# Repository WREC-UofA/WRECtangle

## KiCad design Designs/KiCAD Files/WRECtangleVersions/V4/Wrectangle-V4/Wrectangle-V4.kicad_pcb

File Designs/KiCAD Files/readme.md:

This is where we'll put KiCAD projects / updates.

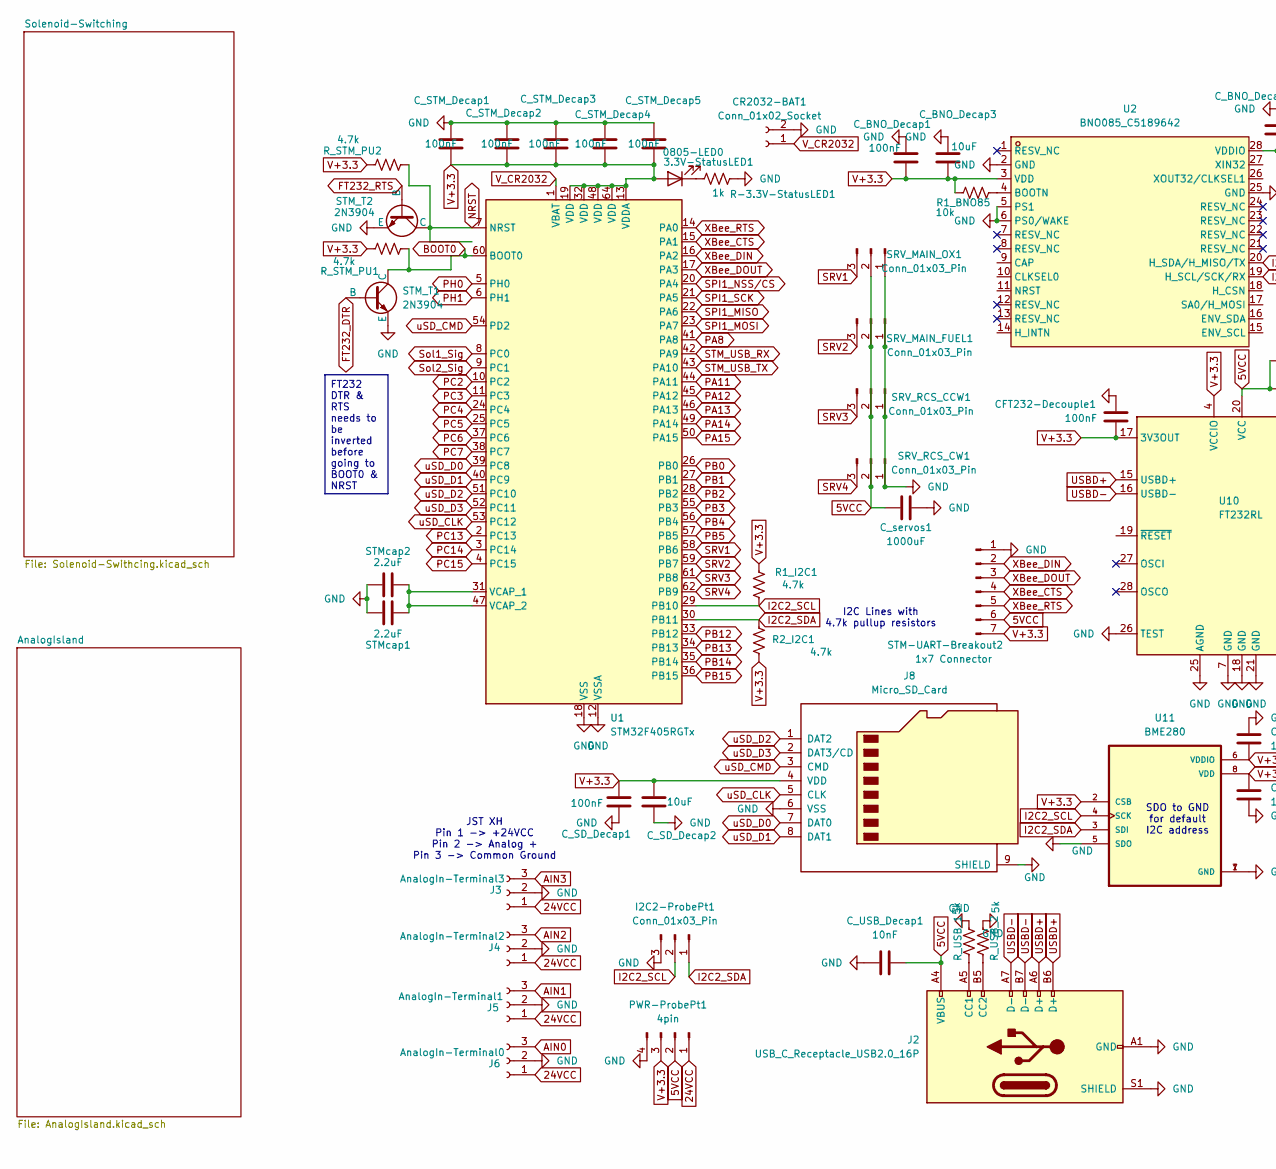
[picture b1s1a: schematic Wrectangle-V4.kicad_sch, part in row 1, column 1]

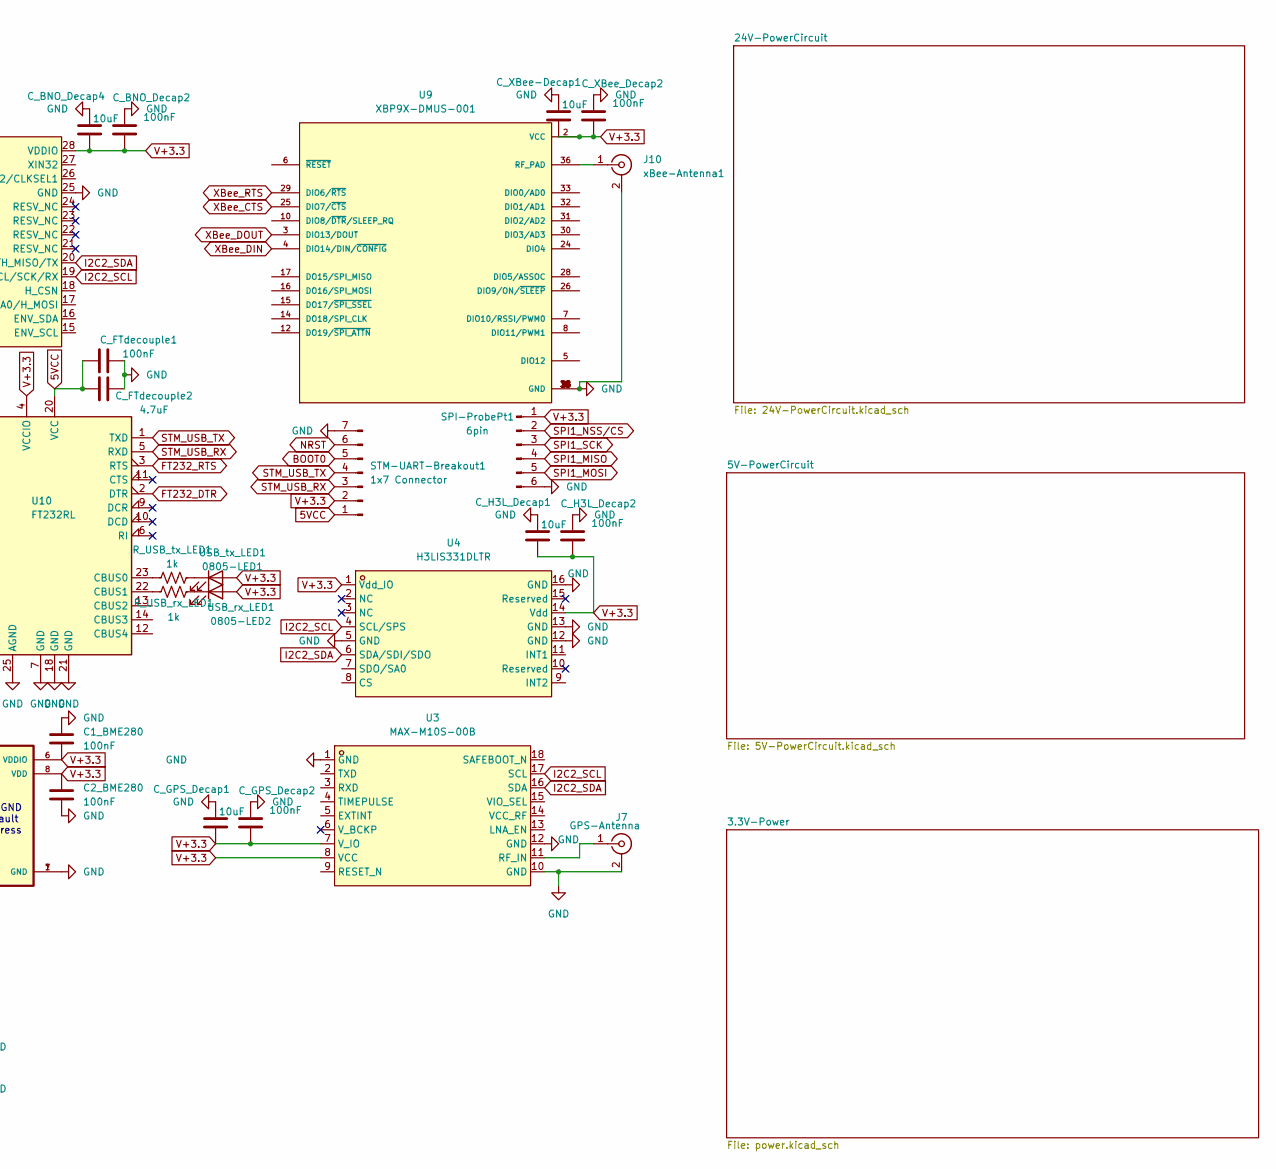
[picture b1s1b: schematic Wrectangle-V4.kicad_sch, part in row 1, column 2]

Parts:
3.3V-StatusLED1: 0805-LED0; LED_0805_2012Metric_Pad1.15x1.40mm_HandSolder
C1_BME280, C2_BME280: 100nF; C_0805_2012Metric_Pad1.18x1.45mm_HandSolder
CFT232-Decouple1: 100nF; C_0805_2012Metric_Pad1.18x1.45mm_HandSolder
CR2032-BAT1: Conn_01x02_Socket; BatteryHolder_Keystone_1060_1x2032
C_BNO_Decap1, C_BNO_Decap2: 100nF; C_0603_1608Metric_Pad1.08x0.95mm_HandSolder
C_BNO_Decap3, C_BNO_Decap4: 10uF; C_0603_1608Metric_Pad1.08x0.95mm_HandSolder
C_FTdecouple1: 100nF; C_0805_2012Metric_Pad1.18x1.45mm_HandSolder
C_FTdecouple2: 4.7uF; C_0805_2012Metric_Pad1.18x1.45mm_HandSolder
C_GPS_Decap1: 10uF; C_0603_1608Metric_Pad1.08x0.95mm_HandSolder
C_GPS_Decap2: 100nF; C_0603_1608Metric_Pad1.08x0.95mm_HandSolder
C_H3L_Decap1: 10uF; C_0603_1608Metric_Pad1.08x0.95mm_HandSolder
C_H3L_Decap2: 100nF; C_0603_1608Metric_Pad1.08x0.95mm_HandSolder
C_SD_Decap1: 100nF; C_0603_1608Metric_Pad1.08x0.95mm_HandSolder
C_SD_Decap2: 10uF; C_0603_1608Metric_Pad1.08x0.95mm_HandSolder
C_STM_Decap1, C_STM_Decap2, C_STM_Decap3, C_STM_Decap4, C_STM_Decap5: 100nF; C_0603_1608Metric_Pad1.08x0.95mm_HandSolder
C_USB_Decap1: 10nF; C_0805_2012Metric_Pad1.18x1.45mm_HandSolder
C_XBee-Decap1: 10uF; C_0603_1608Metric_Pad1.08x0.95mm_HandSolder
C_XBee_Decap2: 100nF; C_0603_1608Metric_Pad1.08x0.95mm_HandSolder
C_servos1: 1000uF; CP_Radial_D10.0mm_P5.00mm
I2C2-ProbePt1: Conn_01x03_Pin; PinHeader_1x03_P2.54mm_Vertical
J2: USB_C_Receptacle_USB2.0_16P; USB_C_Receptacle_Amphenol_124019772112A
J3: AnalogIn-Terminal3; JST_XH_B3B-XH-AM_1x03_P2.50mm_Vertical
J4: AnalogIn-Terminal2; JST_XH_B3B-XH-AM_1x03_P2.50mm_Vertical
J5: AnalogIn-Terminal1; JST_XH_B3B-XH-AM_1x03_P2.50mm_Vertical
J6: AnalogIn-Terminal0; JST_XH_B3B-XH-AM_1x03_P2.50mm_Vertical
J7: GPS-Antenna; SMA_Amphenol_901-144_Vertical; PARTREV C4
J8: Micro_SD_Card; microSD_HC_Wuerth_693072010801
J10: xBee-Antenna1; SMA_Amphenol_901-144_Vertical
PWR-ProbePt1: 4pin; PinHeader_1x04_P2.54mm_Vertical
R1_BNO85: 10k; R_Axial_DIN0204_L3.6mm_D1.6mm_P2.54mm_Vertical
R1_I2C1, R2_I2C1: 4.7k; C_0603_1608Metric_Pad1.08x0.95mm_HandSolder
R-3.3V-StatusLED1: 1k; LED_0805_2012Metric_Pad1.15x1.40mm_HandSolder
R_STM_PU1, R_STM_PU2: 4.7k; C_0603_1608Metric_Pad1.08x0.95mm_HandSolder
R_USB_1, R_USB_2: 5k; R_1206_3216Metric_Pad1.30x1.75mm_HandSolder
R_USB_rx_LED1: 1k; R_0805_2012Metric_Pad1.20x1.40mm_HandSolder
R_USB_tx_LED1: 1k; R_0805_2012Metric_Pad1.20x1.40mm_HandSolder
SPI-ProbePt1: 6pin; PinHeader_1x06_P2.54mm_Vertical
SRV_MAIN_FUEL1: Conn_01x03_Pin; PinHeader_1x03_P2.54mm_Vertical
SRV_MAIN_OX1: Conn_01x03_Pin; PinHeader_1x03_P2.54mm_Vertical
SRV_RCS_CCW1: Conn_01x03_Pin; PinHeader_1x03_P2.54mm_Vertical
SRV_RCS_CW1: Conn_01x03_Pin; PinHeader_1x03_P2.54mm_Vertical
STM-UART-Breakout1, STM-UART-Breakout2: 1x7 Connector; PinHeader_1x05_P2.54mm_Vertical
STM_T1, STM_T2: 2N3904; TO-92L
STMcap1, STMcap2: 2.2uF; C_0603_1608Metric_Pad1.08x0.95mm_HandSolder
U1: STM32F405RGTx; LQFP-64_10x10mm_P0.5mm
U2: BNO085_C5189642; IC_BNO085; LCSC Part C5189642
U3: MAX-M10S-00B; XCVR_MAX-M10S-00B; LCSC Part C4153167
U4: H3LIS331DLTR; QFN300X300X100-16N; LCSC Part C2655074
U9: XBP9X-DMUS-001; XCVR_XBP9X-DMUS-001; PARTREV K
U10: FT232RL; SSOP-28_5.3x10.2mm_P0.65mm
U11: BME280; PSON65P250X250X100-8N
USB_rx_LED1: 0805-LED2; LED_0805_2012Metric_Pad1.15x1.40mm_HandSolder
USB_tx_LED1: 0805-LED1; LED_0805_2012Metric_Pad1.15x1.40mm_HandSolder

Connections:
0: C1_BME280.1, C2_BME280.2, CFT232-Decouple1.1, CR2032-BAT1.2, C_BNO_Decap1.1, C_BNO_Decap2.1, C_BNO_Decap3.1, C_BNO_Decap4.1, C_FTdecouple1.2, C_FTdecouple2.2, C_GPS_Decap1.1, C_GPS_Decap2.1, C_H3L_Decap1.1, C_H3L_Decap2.1, C_SD_Decap1.1, C_SD_Decap2.1, C_STM_Decap1.1, C_STM_Decap2.1, C_STM_Decap3.1, C_STM_Decap4.1, C_STM_Decap5.1, C_USB_Decap1.1, C_XBee-Decap1.1, C_XBee_Decap2.1, C_servos1.2, I2C2-ProbePt1.3, J2.A1 (GND), J2.A12 (GND), J2.B1 (GND), J2.B12 (GND), J2.S1 (SHIELD), J3.2, J4.2, J5.2, J6.2, J7.2 (Ext), J8.6 (VSS), J8.9 (SHIELD), J10.2 (Ext), PWR-ProbePt1.4, R-3.3V-StatusLED1.1, R_USB_1.1, R_USB_2.1, SPI-ProbePt1.6, SRV_MAIN_FUEL1.1, SRV_MAIN_OX1.1, SRV_RCS_CCW1.1, SRV_RCS_CW1.1, STM-UART-Breakout1.7, STM-UART-Breakout2.1, STM_T1.1 (E), STM_T2.1 (E), STMcap1.1, STMcap2.1, U1.12 (VSSA), U1.18 (VSS), U1.63 (VSS), U2.2 (GND), U2.5 (PS1), U2.6 (PS0/WAKE), U2.25 (GND), U3.1 (GND), U3.10 (GND), U3.12 (GND), U4.5 (GND), U4.12 (GND), U4.13 (GND), U4.16 (GND), U9.1 (GND), U9.11 (GND), U9.13 (GND), U9.22 (GND), U9.35 (GND), U9.38 (GND), U10.7 (GND), U10.18 (GND), U10.21 (GND), U10.25 (AGND), U10.26 (TEST), U11.1 (GND), U11.5 (SDO), U11.7 (GND); also elsewhere on the board
5VCC: C_FTdecouple1.1, C_FTdecouple2.1, C_USB_Decap1.2, C_servos1.1, J2.A4 (VBUS), J2.A9 (VBUS), J2.B4 (VBUS), J2.B9 (VBUS), PWR-ProbePt1.2, SRV_MAIN_FUEL1.2, SRV_MAIN_OX1.2, SRV_RCS_CCW1.2, SRV_RCS_CW1.2, STM-UART-Breakout1.1, STM-UART-Breakout2.6, U10.20 (VCC); also elsewhere on the board
24VCC: J3.1, J4.1, J5.1, J6.1, PWR-ProbePt1.1; also elsewhere on the board
AIN0: J6.3; also elsewhere on the board
AIN1: J5.3; also elsewhere on the board
AIN2: J4.3; also elsewhere on the board
AIN3: J3.3; also elsewhere on the board
BOOT0: R_STM_PU1.2, STM-UART-Breakout1.5, STM_T1.3 (C), U1.60 (BOOT0)
FT232_DTR: STM_T1.2 (B), U10.2 (DTR)
FT232_RTS: STM_T2.2 (B), U10.3 (RTS)
I2C2_SCL: I2C2-ProbePt1.2, R1_I2C1.2, U1.29 (PB10), U2.19 (H_SCL/SCK/RX), U3.17 (SCL), U4.4 (SCL/SPS), U11.4 (SCK)
I2C2_SDA: I2C2-ProbePt1.1, R2_I2C1.1, U1.30 (PB11), U2.20 (H_SDA/H_MISO/TX), U3.16 (SDA), U4.6 (SDA/SDI/SDO), U11.3 (SDI)
NRST: R_STM_PU2.2, STM-UART-Breakout1.6, STM_T2.3 (C), U1.7 (NRST)
unnamed: 3.3V-StatusLED1.1 (K), R-3.3V-StatusLED1.2
unnamed: J2.A5 (CC1), R_USB_1.2
unnamed: J2.B5 (CC2), R_USB_2.2
unnamed: J7.1 (In), U3.11 (RF_IN)
unnamed: J10.1 (In), U9.36 (RF_PAD)
unnamed: STMcap1.2, STMcap2.2, U1.31 (VCAP_1), U1.47 (VCAP_2)
unnamed: R1_BNO85.1, U2.4 (BOOTN)
unnamed: R_USB_tx_LED1.1, U10.23 (CBUS0)
unnamed: R_USB_rx_LED1.1, U10.22 (CBUS1)
unnamed: R_USB_rx_LED1.2, USB_rx_LED1.1 (K)
unnamed: R_USB_tx_LED1.2, USB_tx_LED1.1 (K)
PA8: U1.41 (PA8)
PA11: U1.44 (PA11)
PA12: U1.45 (PA12)
PA13: U1.46 (PA13)
PA14: U1.49 (PA14)
PA15: U1.50 (PA15)
PB0: U1.26 (PB0)
PB1: U1.27 (PB1)
PB2: U1.28 (PB2)
PB3: U1.55 (PB3)
PB4: U1.56 (PB4)
PB5: U1.57 (PB5)
PB12: U1.33 (PB12)
PB13: U1.34 (PB13)
PB14: U1.35 (PB14)
PB15: U1.36 (PB15)
PC2: U1.10 (PC2)
PC3: U1.11 (PC3)
PC4: U1.24 (PC4)
PC5: U1.25 (PC5)
PC6: U1.37 (PC6)
PC7: U1.38 (PC7)
PC13: U1.2 (PC13)
PC14: U1.3 (PC14)
PC15: U1.4 (PC15)
PH0: U1.5 (PH0)
PH1: U1.6 (PH1)
SPI1_MISO: SPI-ProbePt1.4, U1.22 (PA6); also elsewhere on the board
SPI1_MOSI: SPI-ProbePt1.5, U1.23 (PA7); also elsewhere on the board
SPI1_NSS/CS: SPI-ProbePt1.2, U1.20 (PA4); also elsewhere on the board
SPI1_SCK: SPI-ProbePt1.3, U1.21 (PA5); also elsewhere on the board
SRV1: SRV_MAIN_OX1.3, U1.58 (PB6)
SRV2: SRV_MAIN_FUEL1.3, U1.59 (PB7)
SRV3: SRV_RCS_CCW1.3, U1.61 (PB8)
SRV4: SRV_RCS_CW1.3, U1.62 (PB9)
STM_USB_RX: STM-UART-Breakout1.3, U1.42 (PA9), U10.5 (RXD)
STM_USB_TX: STM-UART-Breakout1.4, U1.43 (PA10), U10.1 (TXD)
Sol1_Sig: U1.8 (PC0); also elsewhere on the board
Sol2_Sig: U1.9 (PC1); also elsewhere on the board
USBD+: J2.A6 (D+), J2.B6 (D+), U10.15 (USBD+)
USBD-: J2.A7 (D-), J2.B7 (D-), U10.16 (USBD-)
V+3.3: 3.3V-StatusLED1.2 (A), C1_BME280.2, C2_BME280.1, CFT232-Decouple1.2, C_BNO_Decap1.2, C_BNO_Decap2.2, C_BNO_Decap3.2, C_BNO_Decap4.2, C_GPS_Decap1.2, C_GPS_Decap2.2, C_H3L_Decap1.2, C_H3L_Decap2.2, C_SD_Decap1.2, C_SD_Decap2.2, C_STM_Decap1.2, C_STM_Decap2.2, C_STM_Decap3.2, C_STM_Decap4.2, C_STM_Decap5.2, C_XBee-Decap1.2, C_XBee_Decap2.2, J8.4 (VDD), PWR-ProbePt1.3, R1_BNO85.2, R1_I2C1.1, R2_I2C1.2, R_STM_PU1.1, R_STM_PU2.1, SPI-ProbePt1.1, STM-UART-Breakout1.2, STM-UART-Breakout2.7, U1.13 (VDDA), U1.19 (VDD), U1.32 (VDD), U1.48 (VDD), U1.64 (VDD), U2.3 (VDD), U2.28 (VDDIO), U3.7 (V_IO), U3.8 (VCC), U4.1 (Vdd_IO), U4.14 (Vdd), U9.2 (VCC), U10.4 (VCCIO), U10.17 (3V3OUT), U11.2 (CSB), U11.6 (VDDIO), U11.8 (VDD), USB_rx_LED1.2 (A), USB_tx_LED1.2 (A); also elsewhere on the board
V_CR2032: CR2032-BAT1.1, U1.1 (VBAT)
XBee_CTS: STM-UART-Breakout2.4, U1.15 (PA1), U9.25 (DIO7/~CTS)
XBee_DIN: STM-UART-Breakout2.2, U1.16 (PA2), U9.4 (DIO14/DIN/~CONFIG)
XBee_DOUT: STM-UART-Breakout2.3, U1.17 (PA3), U9.3 (DIO13/DOUT)
XBee_RTS: STM-UART-Breakout2.5, U1.14 (PA0), U9.29 (DIO6/~RTS)
uSD_CLK: J8.5 (CLK), U1.53 (PC12)
uSD_CMD: J8.3 (CMD), U1.54 (PD2)
uSD_D0: J8.7 (DAT0), U1.39 (PC8)
uSD_D1: J8.8 (DAT1), U1.40 (PC9)
uSD_D2: J8.1 (DAT2), U1.51 (PC10)
uSD_D3: J8.2 (DAT3/CD), U1.52 (PC11)

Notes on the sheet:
I2C Lines with 4.7k pullup resistors
JST XH Pin 1 -> +24VCC Pin 2 -> Analog + Pin 3 -> Common Ground
SDO to GND for default I2C address
FT232 DTR & RTS needs to be inverted before going to BOOT0 & NRST

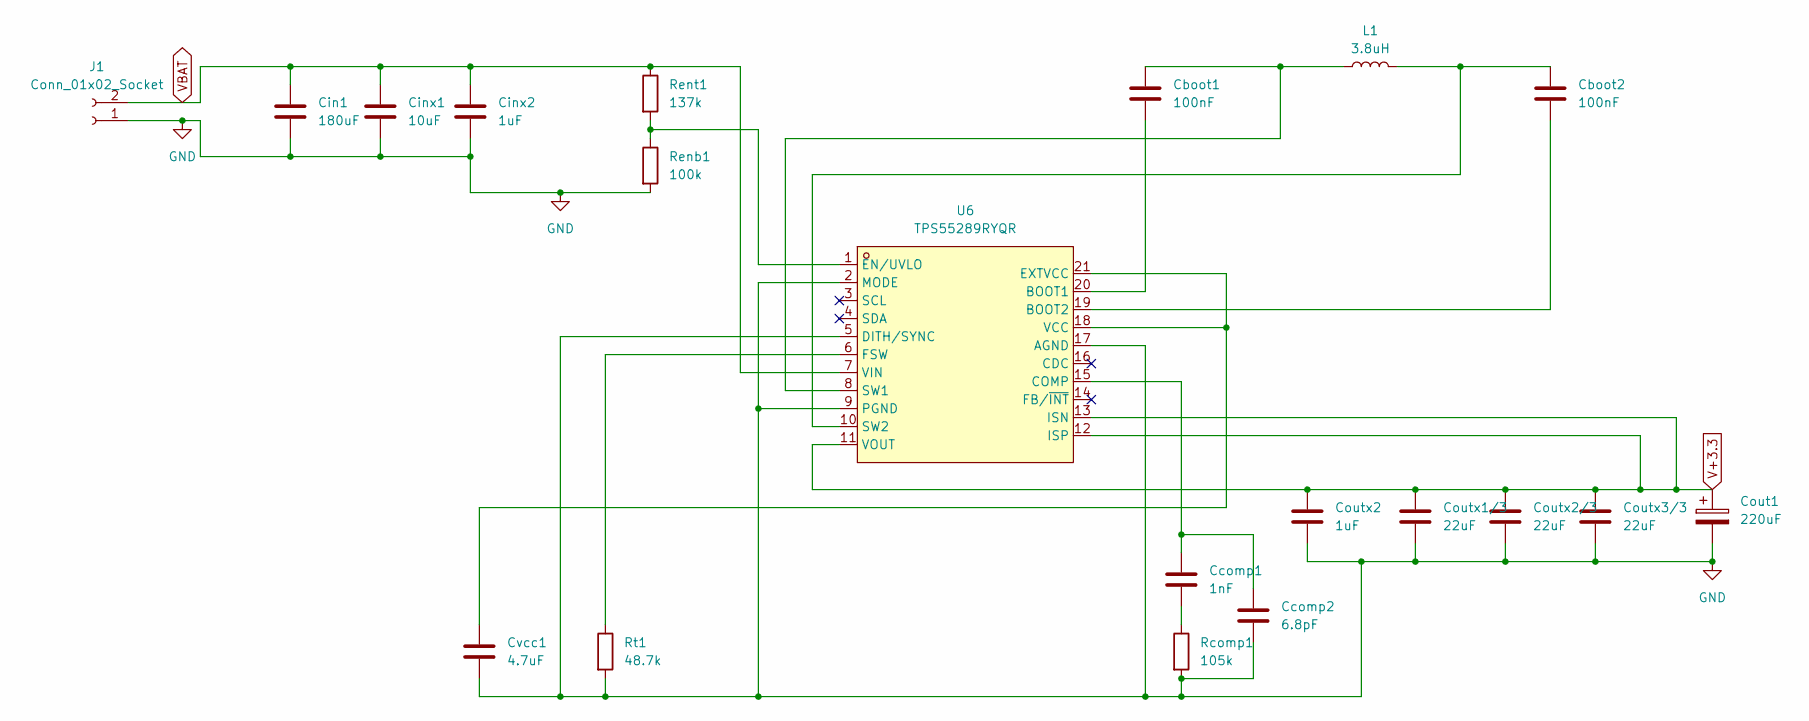
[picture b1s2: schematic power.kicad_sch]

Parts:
Cboot1, Cboot2: 100nF; C_0805_2012Metric_Pad1.18x1.45mm_HandSolder
Ccomp1: 1nF; C_0805_2012Metric_Pad1.18x1.45mm_HandSolder
Ccomp2: 6.8pF; C_0805_2012Metric_Pad1.18x1.45mm_HandSolder
Cin1: 180uF; CP_Elec_8x11.9
Cinx1: 10uF; C_1210_3225Metric_Pad1.33x2.70mm_HandSolder
Cinx2: 1uF; C_0805_2012Metric_Pad1.18x1.45mm_HandSolder
Cout1: 220uF; C_Elec_6.3x5.8
Coutx1/3, Coutx2/3, Coutx3/3: 22uF; C_1210_3225Metric_Pad1.33x2.70mm_HandSolder
Coutx2: 1uF; C_0805_2012Metric_Pad1.18x1.45mm_HandSolder
Cvcc1: 4.7uF; C_0805_2012Metric_Pad1.18x1.45mm_HandSolder
J1: Conn_01x02_Socket; AMASS_XT60-F_1x02_P7.20mm_Vertical
L1: 3.8uH; L_APV_APH0850
Rcomp1: 105k; C_0603_1608Metric_Pad1.08x0.95mm_HandSolder
Renb1: 100k; C_0603_1608Metric_Pad1.08x0.95mm_HandSolder
Rent1: 137k; C_0603_1608Metric_Pad1.08x0.95mm_HandSolder
Rt1: 48.7k; C_0402_1005Metric_Pad0.74x0.62mm_HandSolder
U6: TPS55289RYQR; VREG_TPS55289RYQR; LCSC Part C5942077

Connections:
0: Ccomp2.2, Cin1.2, Cinx1.2, Cinx2.2, Cout1.2, Coutx1/3.2, Coutx2.2, Coutx2/3.2, Coutx3/3.2, Cvcc1.2, J1.1, Rcomp1.2, Renb1.2, Rt1.2, U6.2 (MODE), U6.5 (DITH/SYNC), U6.9 (PGND), U6.17 (AGND); also elsewhere on the board
unnamed: Ccomp1.2, Rcomp1.1
unnamed: Cboot1.2, U6.20 (BOOT1)
unnamed: Cboot2.2, U6.19 (BOOT2)
unnamed: Ccomp1.1, Ccomp2.1, U6.15 (COMP)
unnamed: Renb1.1, Rent1.2, U6.1 (EN/UVLO)
unnamed: Cvcc1.1, U6.18 (VCC), U6.21 (EXTVCC)
unnamed: Rt1.1, U6.6 (FSW)
unnamed: Cboot1.1, L1.1, U6.8 (SW1)
unnamed: Cboot2.1, L1.2, U6.10 (SW2)
V+3.3: Cout1.1, Coutx1/3.1, Coutx2.1, Coutx2/3.1, Coutx3/3.1, U6.11 (VOUT), U6.12 (ISP), U6.13 (ISN); also elsewhere on the board
VBAT: Cin1.1, Cinx1.1, Cinx2.1, J1.2, Rent1.1, U6.7 (VIN); also elsewhere on the board

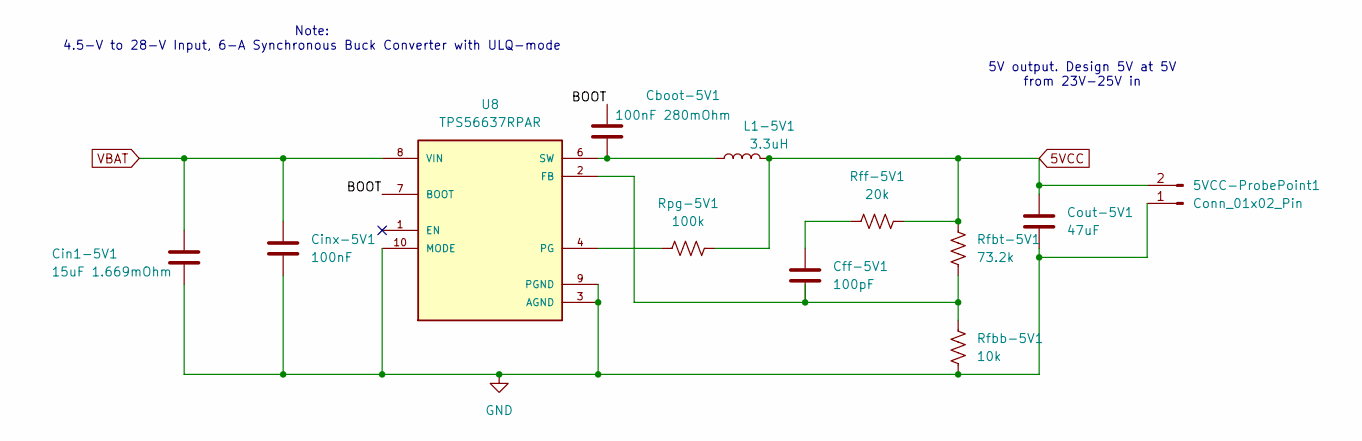
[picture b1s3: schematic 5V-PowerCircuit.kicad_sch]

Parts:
5VCC-ProbePoint1: Conn_01x02_Pin; PinHeader_1x02_P2.54mm_Vertical
Cboot-5V1: 100nF 280mOhm; C_0805_2012Metric_Pad1.18x1.45mm_HandSolder
Cff-5V1: 100pF; C_0805_2012Metric_Pad1.18x1.45mm_HandSolder
Cin1-5V1: 15uF 1.669mOhm; C_0805_2012Metric_Pad1.18x1.45mm_HandSolder
Cinx-5V1: 100nF; C_0805_2012Metric_Pad1.18x1.45mm_HandSolder
Cout-5V1: 47uF; C_1210_3225Metric_Pad1.33x2.70mm_HandSolder
L1-5V1: 3.3uH; IHLP3232DZER330M11
Rfbb-5V1: 10k; C_0603_1608Metric_Pad1.08x0.95mm_HandSolder
Rfbt-5V1: 73.2k; R_0805_2012Metric_Pad1.20x1.40mm_HandSolder
Rff-5V1: 20k; R_0805_2012Metric_Pad1.20x1.40mm_HandSolder
Rpg-5V1: 100k; R_0805_2012Metric_Pad1.20x1.40mm_HandSolder
U8: TPS56637RPAR; CONV_TPS56637RPAR; PARTREV A

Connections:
0: 5VCC-ProbePoint1.1, Cin1-5V1.2, Cinx-5V1.2, Cout-5V1.1, Rfbb-5V1.2, U8.3 (AGND), U8.9 (PGND), U8.10 (MODE); also elsewhere on the board
5VCC: 5VCC-ProbePoint1.2, Cout-5V1.2, L1-5V1.2, Rfbt-5V1.1, Rff-5V1.1, Rpg-5V1.1; also elsewhere on the board
/5V-PowerCircuit/BOOT: Cboot-5V1.2, U8.7 (BOOT)
unnamed: Cff-5V1.1, Rff-5V1.2
unnamed: Cff-5V1.2, Rfbb-5V1.1, Rfbt-5V1.2, U8.2 (FB)
unnamed: Rpg-5V1.2, U8.4 (PG)
unnamed: Cboot-5V1.1, L1-5V1.1, U8.6 (SW)
VBAT: Cin1-5V1.1, Cinx-5V1.1, U8.8 (VIN); also elsewhere on the board

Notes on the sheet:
Note: 4.5-V to 28-V Input, 6-A Synchronous Buck Converter with ULQ-mode
5V output. Design 5V at 5V from 23V-25V in

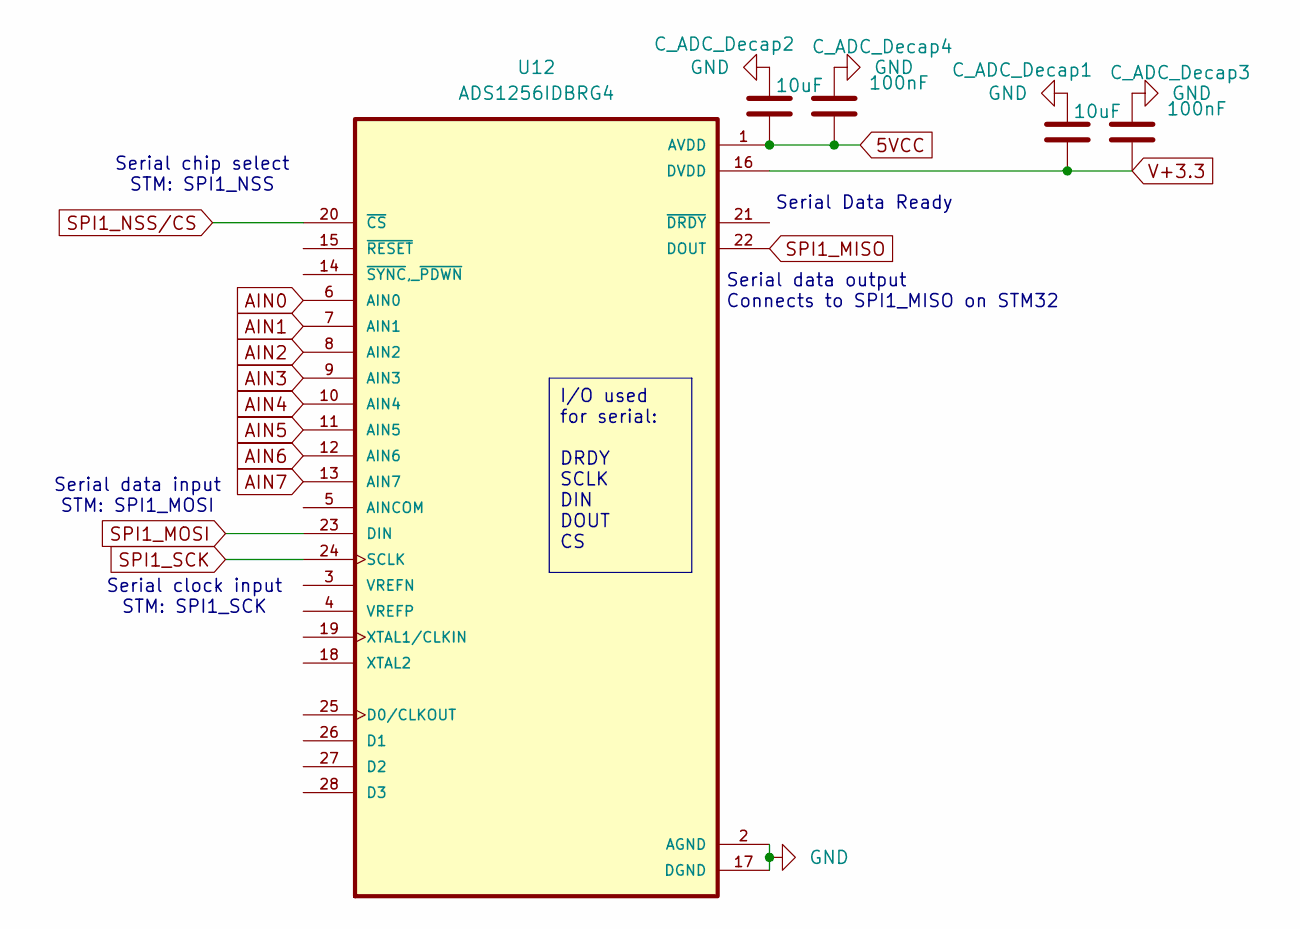
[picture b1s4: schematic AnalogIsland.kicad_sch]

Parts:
C_ADC_Decap1, C_ADC_Decap2: 10uF; C_0603_1608Metric_Pad1.08x0.95mm_HandSolder
C_ADC_Decap3, C_ADC_Decap4: 100nF; C_0603_1608Metric_Pad1.08x0.95mm_HandSolder
U12: ADS1256IDBRG4; SOP65P780X200-28N

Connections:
0: C_ADC_Decap1.1, C_ADC_Decap2.1, C_ADC_Decap3.1, C_ADC_Decap4.1, U12.2 (AGND), U12.17 (DGND); also elsewhere on the board
5VCC: C_ADC_Decap2.2, C_ADC_Decap4.2, U12.1 (AVDD); also elsewhere on the board
AIN0: U12.6 (AIN0); also elsewhere on the board
AIN1: U12.7 (AIN1); also elsewhere on the board
AIN2: U12.8 (AIN2); also elsewhere on the board
AIN3: U12.9 (AIN3); also elsewhere on the board
AIN4: U12.10 (AIN4)
AIN5: U12.11 (AIN5)
AIN6: U12.12 (AIN6)
AIN7: U12.13 (AIN7)
SPI1_MISO: U12.22 (DOUT); also elsewhere on the board
SPI1_MOSI: U12.23 (DIN); also elsewhere on the board
SPI1_NSS/CS: U12.20 (~CS); also elsewhere on the board
SPI1_SCK: U12.24 (SCLK); also elsewhere on the board
V+3.3: C_ADC_Decap1.2, C_ADC_Decap3.2, U12.16 (DVDD); also elsewhere on the board

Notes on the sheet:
Serial data output Connects to SPI1_MISO on STM32
Serial data input STM: SPI1_MOSI
Serial Data Ready
Serial clock input STM: SPI1_SCK
Serial chip select STM: SPI1_NSS
I/O used for serial: DRDY SCLK DIN DOUT CS

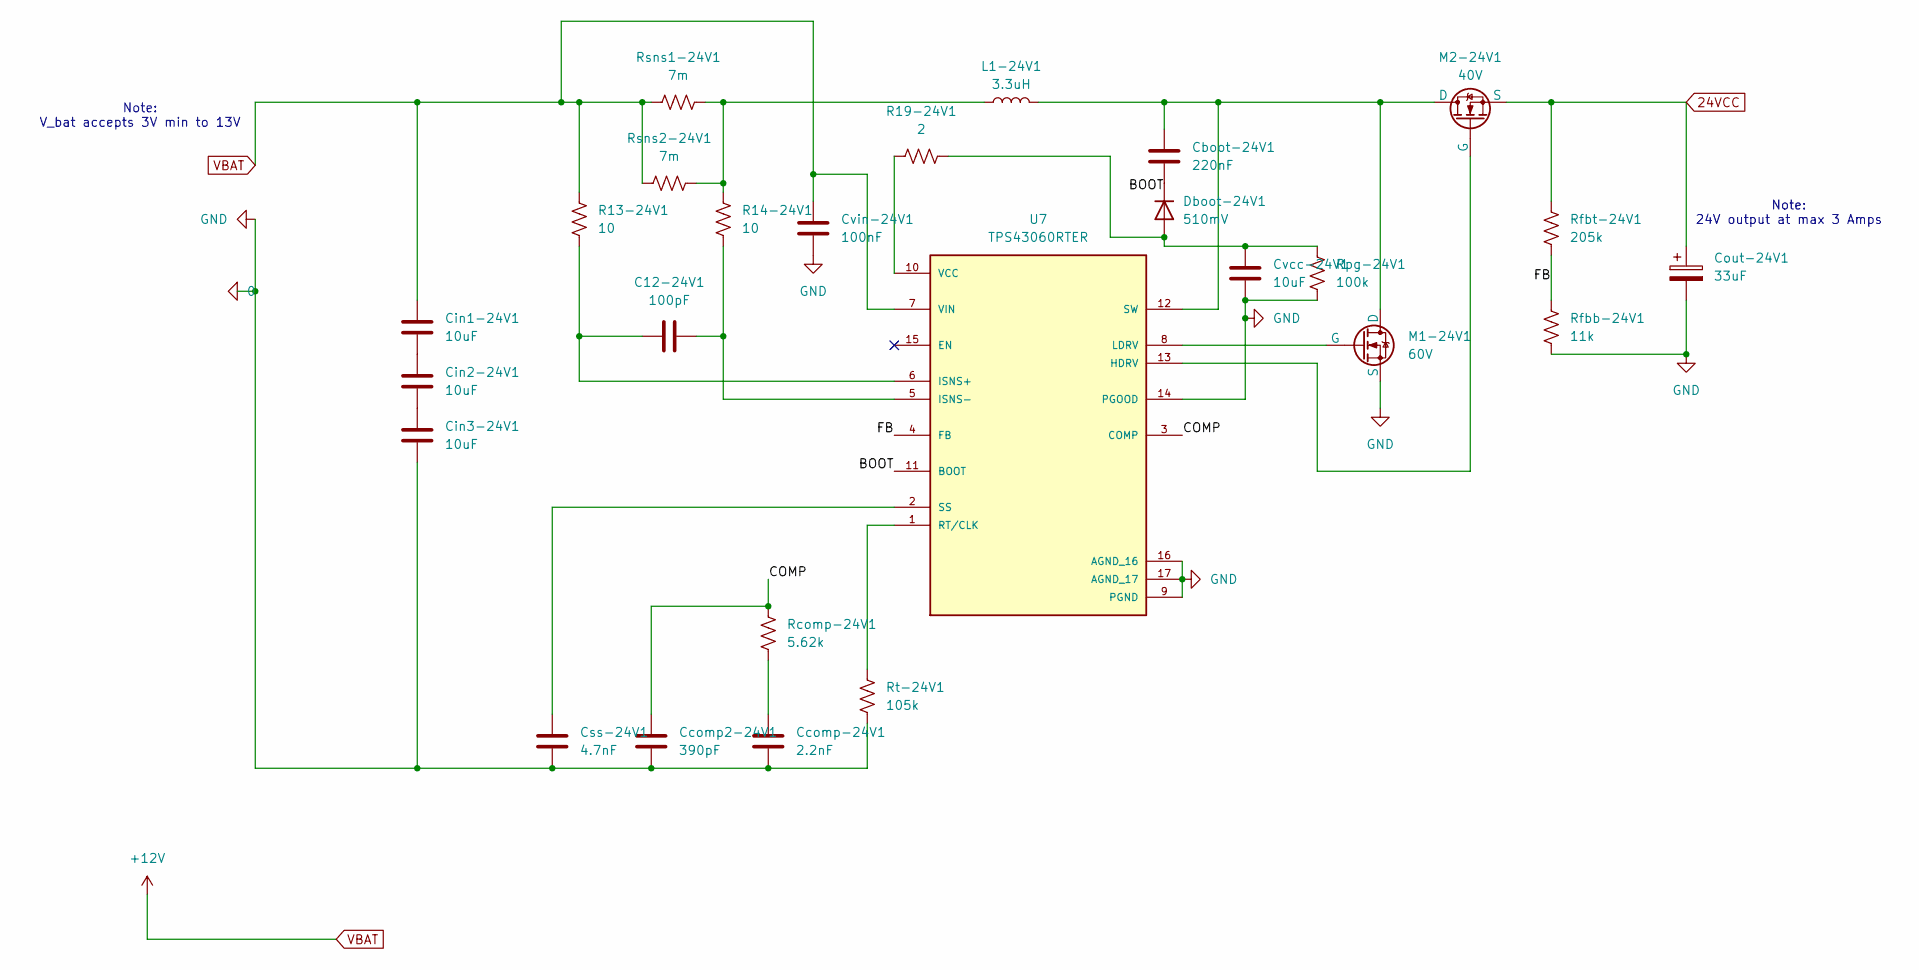
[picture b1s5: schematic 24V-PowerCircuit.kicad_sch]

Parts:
C12-24V1: 100pF; C_0805_2012Metric_Pad1.18x1.45mm_HandSolder
Cboot-24V1: 220nF; C_0805_2012Metric_Pad1.18x1.45mm_HandSolder
Ccomp2-24V1: 390pF; C_0805_2012Metric_Pad1.18x1.45mm_HandSolder
Ccomp-24V1: 2.2nF; C_0805_2012Metric_Pad1.18x1.45mm_HandSolder
Cin1-24V1, Cin2-24V1, Cin3-24V1: 10uF; C_1210_3225Metric_Pad1.33x2.70mm_HandSolder
Cout-24V1: 33uF; CP_Elec_6.3x7.7
Css-24V1: 4.7nF; C_0805_2012Metric_Pad1.18x1.45mm_HandSolder
Cvcc-24V1: 10uF; C_0805_2012Metric_Pad1.18x1.45mm_HandSolder
Cvin-24V1: 100nF; C_0805_2012Metric_Pad1.18x1.45mm_HandSolder
Dboot-24V1: 510mV; D_SOD-123F
L1-24V1: 3.3uH; L_Coilcraft_XAL7070-XXX
M1-24V1: 60V; TRANS_CSD18543Q3A
M2-24V1: 40V; MOSFET_CSD19531Q5A
R13-24V1, R14-24V1: 10; C_0603_1608Metric_Pad1.08x0.95mm_HandSolder
R19-24V1: 2; C_0603_1608Metric_Pad1.08x0.95mm_HandSolder
Rcomp-24V1: 5.62k; C_0603_1608Metric_Pad1.08x0.95mm_HandSolder
Rfbb-24V1: 11k; R_0805_2012Metric_Pad1.20x1.40mm_HandSolder
Rfbt-24V1: 205k; R_0805_2012Metric_Pad1.20x1.40mm_HandSolder
Rpg-24V1: 100k; R_0805_2012Metric_Pad1.20x1.40mm_HandSolder
Rsns1-24V1, Rsns2-24V1: 7m; R_0805_2012Metric_Pad1.20x1.40mm_HandSolder
Rt-24V1: 105k; C_0603_1608Metric_Pad1.08x0.95mm_HandSolder
U7: TPS43060RTER; QFN50P300X300X80-17N; PARTREV 4205254/D 01/11

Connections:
0: Ccomp2-24V1.2, Ccomp-24V1.2, Cin3-24V1.2, Cout-24V1.2, Css-24V1.2, Cvcc-24V1.1, Cvin-24V1.1, M1-24V1.3 (S), Rfbb-24V1.1, Rpg-24V1.1, Rt-24V1.2, U7.9 (PGND), U7.14 (PGOOD), U7.16 (AGND_16), U7.17 (AGND_17); also elsewhere on the board
24VCC: Cout-24V1.1, M2-24V1.3 (S), Rfbt-24V1.2; also elsewhere on the board
/24V-PowerCircuit/BOOT: U7.11 (BOOT)
/24V-PowerCircuit/COMP: Ccomp2-24V1.1, Rcomp-24V1.1, U7.3 (COMP)
/24V-PowerCircuit/FB: Rfbb-24V1.2, Rfbt-24V1.1, U7.4 (FB)
unnamed: Ccomp-24V1.1, Rcomp-24V1.2
unnamed: Cin1-24V1.2, Cin2-24V1.1
unnamed: Cin2-24V1.2, Cin3-24V1.1
unnamed: Cvcc-24V1.2, Dboot-24V1.2 (A), R19-24V1.2, Rpg-24V1.2
unnamed: Cboot-24V1.1, Dboot-24V1.1 (K)
unnamed: L1-24V1.1, R14-24V1.2, Rsns1-24V1.2, Rsns2-24V1.2
unnamed: Cboot-24V1.2, L1-24V1.2, M1-24V1.1 (D), M2-24V1.1 (D), U7.12 (SW)
unnamed: M1-24V1.2 (G), U7.8 (LDRV)
unnamed: M2-24V1.2 (G), U7.13 (HDRV)
unnamed: C12-24V1.1, R13-24V1.2, U7.6 (ISNS+)
unnamed: C12-24V1.2, R14-24V1.1, U7.5 (ISNS-)
unnamed: Rt-24V1.1, U7.1 (RT/CLK)
unnamed: Css-24V1.1, U7.2 (SS)
unnamed: R19-24V1.1, U7.10 (VCC)
VBAT: Cin1-24V1.1, Cvin-24V1.2, R13-24V1.1, Rsns1-24V1.1, Rsns2-24V1.1, U7.7 (VIN); also elsewhere on the board

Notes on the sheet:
Note: 24V output at max 3 Amps
Note: V_bat accepts 3V min to 13V

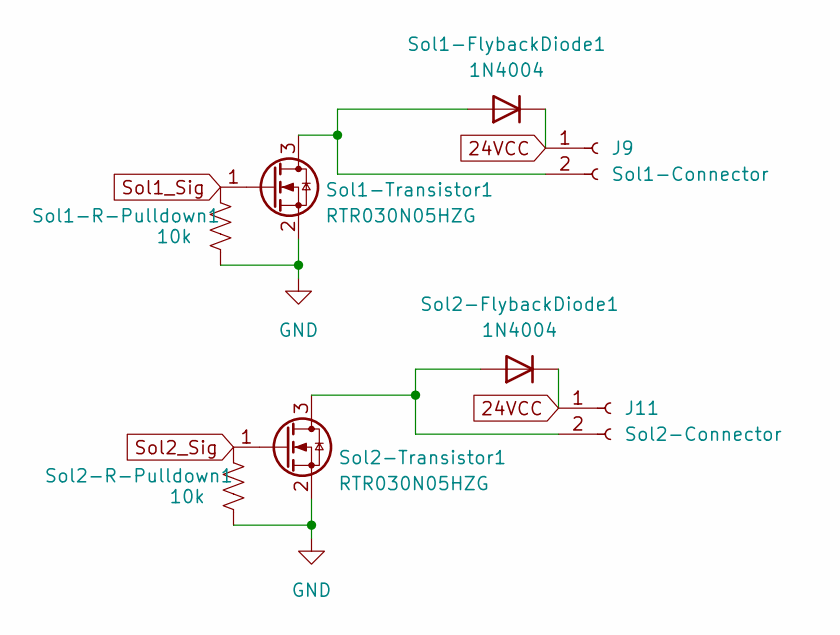
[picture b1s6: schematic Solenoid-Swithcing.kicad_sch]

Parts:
J9: Sol1-Connector; JST_XH_B2B-XH-A_1x02_P2.50mm_Vertical
J11: Sol2-Connector; JST_XH_B2B-XH-A_1x02_P2.50mm_Vertical
Sol1-FlybackDiode1, Sol2-FlybackDiode1: 1N4004; D_DO-41_SOD81_P2.54mm_Vertical_KathodeUp
Sol1-R-Pulldown1, Sol2-R-Pulldown1: 10k; R_Axial_DIN0207_L6.3mm_D2.5mm_P2.54mm_Vertical
Sol1-Transistor1, Sol2-Transistor1: RTR030N05HZG; SOT-323_SC-70_Handsoldering

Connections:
0: Sol1-R-Pulldown1.1, Sol1-Transistor1.2 (S), Sol2-R-Pulldown1.1, Sol2-Transistor1.2 (S); also elsewhere on the board
24VCC: J9.1, J11.1, Sol1-FlybackDiode1.1 (K), Sol2-FlybackDiode1.1 (K); also elsewhere on the board
unnamed: J9.2, Sol1-FlybackDiode1.2 (A), Sol1-Transistor1.3 (D)
unnamed: J11.2, Sol2-FlybackDiode1.2 (A), Sol2-Transistor1.3 (D)
Sol1_Sig: Sol1-R-Pulldown1.2, Sol1-Transistor1.1 (G); also elsewhere on the board
Sol2_Sig: Sol2-R-Pulldown1.2, Sol2-Transistor1.1 (G); also elsewhere on the board

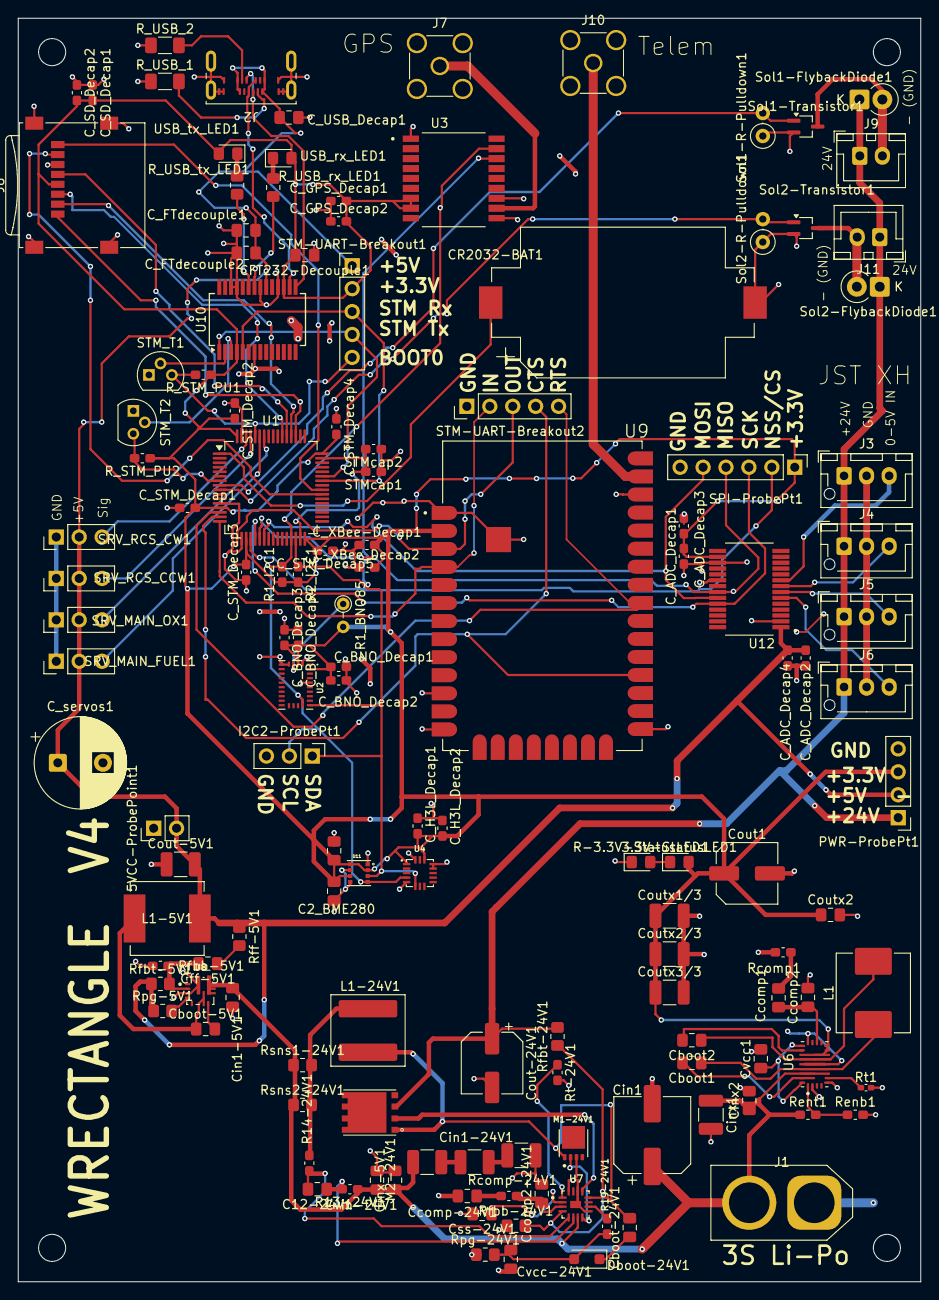
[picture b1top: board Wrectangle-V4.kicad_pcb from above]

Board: 2 copper layers, 100.0 x 140.0 mm, 137 parts (0 on the bottom side), 83 nets.

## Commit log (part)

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2026-02-07 added some basic platformio stuff
2026-02-07 Add solenoid and communication tests
2026-02-07 Breakout Board
    one of many uploads.
2026-02-07 upload a bunch of stuff
2026-02-07 move datasheets
2026-02-13 made folder for schematic of nucleo dev board converted to kicad files
2026-02-13 making new version of board
2026-02-14 test etan
2026-02-14 oops
    Revised PCB review action items for clarity and structure.
2026-02-14 made some minor fixes to pins
    Added DRDY to ADC
2026-02-14 idk nothing pry
